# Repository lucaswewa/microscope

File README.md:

# microscope

Microscope control software. A Rust backend serves the microscope's camera, stage and the routines built on them (autofocus, calibration, slide scanning, timelapse) as [W3C Web of Things](https://www.w3.org/WoT/) Things over HTTP. A Vue 3 and TypeScript web app is the user interface.

- The backend is built on [`teta-wot`](https://github.com/lucaswewa/teta-wot), a Rust framework for Web of Things servers.
- The workflows and feature set are inspired by the [OpenFlexure Microscope](https://openflexure.org/), with an original interface and an independent implementation ([ADR-0002](docs/adr/0002-independent-implementation-of-openflexure-inspired-behaviour.md)). This project is not affiliated with the OpenFlexure project.

## Status

**Milestone 1 is complete:** the whole application, against a simulated camera and XYZ stage, whose images depend on the stage position and focus.

- **Its features match** the OpenFlexure Microscope's: live view, stage control, autofocus, calibration, slide scanning with stitching, timelapse sequences, a gallery, and the Settings, Logging, About and Power pages.
- **It ships a local launcher,** and the app connects to remote microscopes too.
- **The [plan's phase overview](docs/milestone-1/implementation-plan.md#8-phase-overview)** lists every phase, and the [retrospective](docs/milestone-1/retrospective.md) looks back on them.
- **Next:** real cameras and stages follow in milestone 2 ([readiness checklist](docs/milestone-2/readiness.md)), and the web app will later be reused in a Tauri desktop app.

Milestone 1 targets Windows x86_64 ([ADR-0003](docs/adr/0003-milestone-1-platform-windows-x86-64.md)).

## Using the microscope

### Getting it

Download `microscope-<version>-windows-x86_64.zip` from the [releases](https://github.com/lucaswewa/microscope/releases), and unzip it anywhere. It holds:

- `microscope-launcher.exe`, which you run;
- `microscope-server.exe`, which serves the microscope and the app;
- the default configuration, in `configs\`;
- this README, the licence, `NOTICE`, and the licences of the third-party software it includes.

### Running it

1. **Double-click `microscope-launcher.exe`.** A console window opens, and so does the app, in your browser, at <http://127.0.0.1:5000/>, or at another port if 5000 is taken. The window shows the server's messages; keep it open while you work.
2. **The first time,** the calibration wizard opens: follow it to calibrate the camera and how the stage moves in the image.
3. **To stop,** close the window or press Ctrl+C in it, or use the app's Power tab.
4. **Restart,** in the Power tab, starts the server again, and the app reconnects by itself. If the server ever crashes, the launcher starts it again.

Only one launcher runs at a time; a second one says so and ends.

### Where your data lives

Everything is in `%LOCALAPPDATA%\Microscope\` (paste that into File Explorer's address bar):

| Folder or file | What |
|---|---|
| `data\` | Your captures, scans and sequences, which the Gallery shows |
| `settings\` | Calibrations and settings |
| `logs\` | The server's daily logs, and `launcher.log`, everything the window showed |
| `generated-config.json` | The configuration the launcher gives the server; it's written at each start |

### Connecting from another computer

The launcher's server only answers this computer, unless you ask otherwise:

```powershell
.\microscope-launcher.exe --host 0.0.0.0
```

Then, on another computer on the same network, open `http://<this computer's name>:5000/` in a browser. From an app that's already open, use **Settings → Connection → Another microscope** with the same address, such as `lab-pc:5000`.

**There's no password:** anyone who can reach the computer can use the microscope. Do this only on a network you trust. Windows may ask whether to let the server through its firewall.

### Resetting

- **Settings and calibrations:** stop the launcher, delete `%LOCALAPPDATA%\Microscope\settings\`, and start it again. The calibration wizard opens, as the first time. Your captures and scans are kept.
- **Everything,** your captures and scans included: delete the whole `%LOCALAPPDATA%\Microscope\` folder.

### Other options

`microscope-launcher.exe --help` lists them:

- `-c <file>` uses another configuration;
- `--root <folder>` keeps the data somewhere other than `%LOCALAPPDATA%\Microscope\`;
- `--port <number>` prefers another port;
- `--no-browser` doesn't open the app.

### A Zaber stage

[`configs/zaber.json`](configs/zaber.json) drives a Zaber XYZ stage, with the simulated camera ([ADR-0042](docs/adr/0042-zaber-stages-through-the-ascii-protocol.md)):

1. **Find its port:** `microscope-server --list-devices` lists the serial ports.
2. **Configure it:** in a copy of the file, set `port`, such as `COM3` or `/dev/ttyUSB0`. Check each axis's `device` and `axis` numbers; the defaults suit three integrated stages, daisy-chained. Set each axis's `microstep_um`, from its datasheet, for distances in µm.
3. **Run it:** `microscope-launcher -c my-zaber.json`.
4. **Home it,** once the stage is clear, from Settings → Stage. z homes too.

The simulated camera's image doesn't follow the Zaber stage, so autofocus and scans won't work with this file. A real camera's configuration follows with its driver.

### A Basler camera

[`configs/basler-zaber.json`](configs/basler-zaber.json) drives a Basler camera, through [pylon](https://www.baslerweb.com/pylon), and a Zaber stage ([ADR-0044](docs/adr/0044-one-camera-thing-for-every-sdk.md)):

1. **Install pylon,** and plug the camera in. `microscope-server --list-devices` lists it, by serial number.
2. **Configure it:** in a copy of the file, set the camera's `serial_number`, or leave it out for the first camera found, and the stage as above.
3. **Run it,** and calibrate the camera from Settings → Camera, looking at the empty slide: the camera's own automatic exposure and white balance run once, then the background is set.

Settings → Camera has the camera's exposure, gain, pixel format, white balance and binning, as far as it has them. If the camera is unplugged, the server opens it again once it's back.

Without a camera, pylon's emulator stands in: set `PYLON_CAMEMU=1` before starting the server, and the camera `0815-0000` appears.

### On Linux

Linux x86_64 and ARM64, the Raspberry Pi 5 included, have two downloads.

**`microscope-<version>-linux-<arch>.tar.gz`** runs the microscope as on Windows. Unpack it, and run `./microscope-launcher` in a terminal. Everything is in `~/.local/share/microscope/` (or in `$XDG_DATA_HOME`, if that's set), in the same folders as above. Ctrl+C, or closing the terminal, stops it.

**`microscope_<version>_<arch>.deb`** runs the microscope as a service, started at boot, such as on a Pi with no screen:

```sh
sudo apt install ./microscope_0.2.0_arm64.deb
```

- **It serves** <http://127.0.0.1:5000/>, to this machine alone, as the server has no password yet. To reach it from other computers, on a network you trust, set `MICROSCOPE_HOST=0.0.0.0` in `/etc/default/microscope`, then run `sudo systemctl restart microscope`.
- **Its microscope** is in `/etc/microscope/config.json`: the simulated one, at first. Its settings and data are in `/var/lib/microscope/`, and its logs in `/var/log/microscope/` and in `journalctl -u microscope`.
- **Restart,** in the Power tab, starts it again. **Shut down** stops it until `sudo systemctl start microscope`, or the next boot. If it crashes, systemd starts it again; the sixth crash in a minute stops it.
- **Removing it,** `sudo apt remove microscope`, stops the service and keeps `/var/lib/microscope/`.

## Documentation

- [Milestone 1 goals](docs/milestone-1/goals.md)
- [Milestone 1 implementation plan](docs/milestone-1/implementation-plan.md) and [phase specifications](docs/milestone-1/phases.md)
- [Architecture decision records](docs/adr/README.md)
- [Implementation notes](docs/milestone-1/notes/README.md), one per phase, and the [milestone's retrospective](docs/milestone-1/retrospective.md)
- [Milestone 2 readiness checklist](docs/milestone-2/readiness.md)

## Development

### Prerequisites

- Windows x86_64.
- [rustup](https://rustup.rs/), with the MSVC toolchain and Visual Studio's C++ build tools. The repository pins its compiler (Rust 1.98.1) in `rust-toolchain.toml`; `rustup toolchain install` in the repository installs it.
- [Node.js](https://nodejs.org/) 24 LTS, with npm, for the web app.

### Build and check

These are the checks CI runs:

```powershell
cargo fmt --all --check
cargo clippy --workspace --all-targets --locked -- -D warnings
cargo test --workspace --locked
cargo doc --workspace --no-deps --locked   # CI sets RUSTDOCFLAGS=-D warnings
```

### Run the server

```powershell
cargo run -p microscope-server -- -c configs/simulation.json
```

It listens on <http://127.0.0.1:5000/> (`--host` and `--port` change that). The API is under `/api/v1` (for example <http://127.0.0.1:5000/api/v1/health> and <http://127.0.0.1:5000/api/v1/system/>), and the interactive API docs are at <http://127.0.0.1:5000/docs>. Ctrl-C stops it gracefully. `--help` lists the options: `teta-wot`'s, and `--webapp-dir`.

The server also serves the web app, at <http://127.0.0.1:5000/> ([ADR-0016](docs/adr/0016-serving-and-embedding-the-web-app.md)). A debug build reads it from `web/dist`, so build the web app first (`npm run build` in `web/`); without a build, `/` shows a placeholder page. `--webapp-dir <path>` serves it from another folder.

`--list-devices` prints the serial ports and the cameras the drivers find, for writing a configuration ([configs/README.md](configs/README.md)). Basler cameras need [pylon](https://www.baslerweb.com/pylon), and Allied Vision's [Vimba X](https://www.alliedvision.com/en/products/software/vimba-x-sdk/), installed; the server runs without them ([ADR-0041](docs/adr/0041-hardware-drivers.md)).

### Build a release

Build the web app first, then the server, which embeds `web/dist`:

```powershell
cd web
npm ci
npm run build
cd ..
cargo build --release -p microscope-server
```

`target/release/microscope-server.exe -c configs/simulation.json` then serves the API and the app on its own.

The zip a user downloads also needs the launcher's release build and [cargo-about](https://github.com/EmbarkStudios/cargo-about), which lists the Rust crates' licences ([ADR-0035](docs/adr/0035-release-packaging-and-third-party-notices.md)):

```powershell
cargo build --release -p microscope-server -p microscope-launcher --locked
cargo install cargo-about --version 0.9.2 --features cli --locked
./release/package.ps1 -Version 0.2.0
```

It's written to `release-out\`. On Linux, `bash release/package.sh 0.2.0` builds the archive and the `.deb` there instead, with `jq` and `dpkg-deb`. Pushing a tag such as `v0.2.0` has the release workflow build them all, check that each launcher starts and that the `.deb`'s service serves and restarts, and publish them, with the tag's notes from `release/notes/` where there are some.

### Run the launcher

The launcher is the one command a user needs ([ADR-0033](docs/adr/0033-local-launcher-and-its-tauri-successor.md)). It keeps the server's settings, data and logs in `%LOCALAPPDATA%\Microscope`, or on Linux in `~/.local/share/microscope`, starts the server on port 5000 (or another, if that's taken), and opens the app in the browser. It starts the server again when the server asks to restart, or after a crash. Ctrl-C stops both.

```powershell
cargo build -p microscope-server -p microscope-launcher
target\debug\microscope-launcher.exe
```

It runs the `microscope-server` beside it, so build both; a release build, after the web app, gives a server with the app embedded. `-c <config>` uses another configuration, `--no-browser` doesn't open the app, `--root <folder>` keeps everything in another folder, and `--help` lists the rest. Everything the server prints also goes to `logs\launcher.log` in that folder.

Logs go to the console, to daily files in `.microscope/logs/`, and to the server log at <http://127.0.0.1:5000/api/v1/log/>; `/api/v1/logfile/` downloads today's file. `--debug` adds DEBUG events from the application and `teta-wot` ([ADR-0008](docs/adr/0008-server-logging-and-log-endpoints.md)).

The workspace's crates and the rules between them are described in [ADR-0005](docs/adr/0005-repository-layout-and-crate-boundaries.md).

### The web app

The web app is in `web/` ([ADR-0009](docs/adr/0009-frontend-toolchain.md)):

```powershell
cd web
npm ci
npm run dev          # http://localhost:5173/, with /api forwarded to the server on port 5000
```

These are the checks CI runs, plus the end-to-end tests:

```powershell
npm run format:check
npm run lint
npm run typecheck
npm run test:unit
npm run build
npx playwright install chromium   # once per machine
npm run test:e2e                  # builds the app and a server that serves it, on ports 5098 and 5099
```

The end-to-end tests' server keeps its settings, data and logs in a temporary folder, emptied for each run, not in `.microscope`. They include whole workflows, such as a histo scan, and Restart through the launcher, which they build.

The long tests run each night in CI ([`nightly.yml`](.github/workflows/nightly.yml)): a 30-minute soak, streaming and scanning, and the performance budgets. To run them, preferably against a release build:

```powershell
$env:MICROSCOPE_LONG = '1'; $env:MICROSCOPE_SOAK_MINUTES = '30'
npx playwright test --project=long   # soak.json and budgets.json are written under test-results
```

`npm run test:contract` runs the web app's WoT client against a running server, whose API root is `MICROSCOPE_API_URL` (by default `http://127.0.0.1:5000/api/v1/`). CI runs it against a fresh server.

`MICROSCOPE_API_TARGET` points the development proxy at another server, such as `http://lab-pc:5000`.

Two pages exist only in development, each showing light and dark side by side:

- <http://localhost:5173/#/dev/tokens> shows the design tokens ([ADR-0011](docs/adr/0011-design-tokens-and-theming.md));
- <http://localhost:5173/#/dev/components> shows every UI component, with their states and overlays ([ADR-0013](docs/adr/0013-own-components-on-reka-ui-primitives.md)).

Both have an **Accent** picker, to try every accent colour across the whole app: the nine that Settings, Display offers, and 19 more ([ADR-0047](docs/adr/0047-accent-colours-a-person-can-choose.md)). It's the same choice as Settings', kept in this browser. The tokens page shows each pair's contrast in both themes, with those below WCAG AA's minimum in red.

The rules that keep the app ready for a Tauri desktop app are in [ADR-0010](docs/adr/0010-rules-for-a-tauri-ready-web-app.md).

### Contributing

Work proceeds in small phases, each delivered as one pull request that follows the [Definition of Done](docs/milestone-1/implementation-plan.md#7-how-phases-work). [CLAUDE.md](CLAUDE.md) sums up the working rules, for people and for Claude Code sessions.

## Licence

[MIT](LICENSE). Third-party material and its licences are listed in [NOTICE](NOTICE).

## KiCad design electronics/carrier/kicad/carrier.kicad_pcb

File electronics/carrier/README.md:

# The OPTIMA carrier board

The board under the Pico 2. [`optima_carrier_board.md`](../../docs/misc/optima_carrier_board.md) describes it, [`kicad/carrier.pdf`](kicad/carrier.pdf) is its schematic, and [`kicad/fab/`](kicad/fab/) has what a maker needs.

## Changing it

Don't edit the schematic or the board in KiCad: the build replaces them.

1. Change [`circuit.py`](circuit.py) or [`placement.py`](placement.py).
2. Run the build, with KiCad 10 installed:

   ```sh
   python electronics/carrier/make.py
   ```

   It takes about 15 seconds, and prints every check.
3. If you moved a part, or changed a net, route it again (below). The checks fail until you do.
4. Commit the scripts with the rebuilt `kicad/`, `routes.ses` and `REPORT.md`.

`python electronics/carrier/make.py --check` builds into a temporary folder instead. It fails if a check fails, or if `kicad/` or `REPORT.md` isn't what the scripts build. Run it before every pull request. It doesn't compare the PDFs, the Gerbers' zip or the picture, which the rest stand for, or the fill of the pour, which KiCad changes by a few points from run to run.

## Routing it

The build doesn't need a router: it takes the tracks from `routes.ses`. Only a new route needs FreeRouting, which is a tool here, not part of this project:

1. Download `freerouting-2.5.0.jar` from [its release](https://github.com/freerouting/freerouting/releases/tag/v2.5.0), and a Java 25 runtime, such as [Temurin's](https://adoptium.net/temurin/releases/?version=25). Neither needs installing.
2. Run this, leaving out `JAVA` if `java` on your path is Java 25:

   ```sh
   FREEROUTING=path/to/freerouting-2.5.0.jar JAVA=path/to/java python electronics/carrier/make.py --route
   ```

It takes about a minute, and prints how many connections are open after each job. A new route gives a different board each time, so run it again if it stops short of 0, or if a check fails. Then read the copper: the DRC doesn't know about current.

What took some finding, in case FreeRouting changes:

- **The jar, not the command-line build.** Version 2.5.0's `freerouting-cli` crashes on its first board and then hangs ([#957](https://github.com/freerouting/freerouting/issues/957), [#1019](https://github.com/freerouting/freerouting/issues/1019)).
- **A chain of one-pass jobs.** A job's first pass does the work, and its later passes tear up about the GND net's worth of it. So each job starts from the last one's tracks.
- **GND as a net, not a plane.** As a plane, the router counts it as joined while its own tracks cut the pour into islands.
- **Cheaper vias.** At its own cost, it leaves crossings open sooner than use one.
- **Separate processes.** KiCad reads the project's net classes only when it loads a saved board in a new process, or it exports every net in one class. So `board.py` runs in steps.
- **Its options,** in `make.py`. Automatic narrowing and fan-out make tracks thinner than their class. Usage data goes out unless it's turned off, which `make.py` does.

FreeRouting leaves its settings and logs in your user folder: `AppData\Roaming\freerouting` and `AppData\Local\freerouting` on Windows.

## Files

| File | What it does |
|---|---|
| `circuit.py` | The parts and the nets that join their pins |
| `schematic.py` | Draws the circuit as a KiCad schematic, with this board's symbols, and writes the project, with its rules and net classes |
| `footprints.py` | The two footprints KiCad doesn't have |
| `placement.py` | Where each part goes, and the tracks laid out by hand |
| `board.py` | Builds the board in KiCad's Python: the parts, the fixed tracks, the routes and the pour |
| `routes.ses` | The router's tracks. FreeRouting writes this. |
| `checks.py` | Checks the netlist against the circuit, the interlock, the pins, levels and connectors, and the board |
| `make.py` | Runs all that, and KiCad's command line for its checks and the fabrication files |
| `kicad/` | The built KiCad project, netlist and PDF, with the fabrication files in `kicad/fab/` |
| `REPORT.md` | The checks' results |

The symbols and those two footprints are this project's own. The other footprints are named from KiCad's libraries, which allow it.

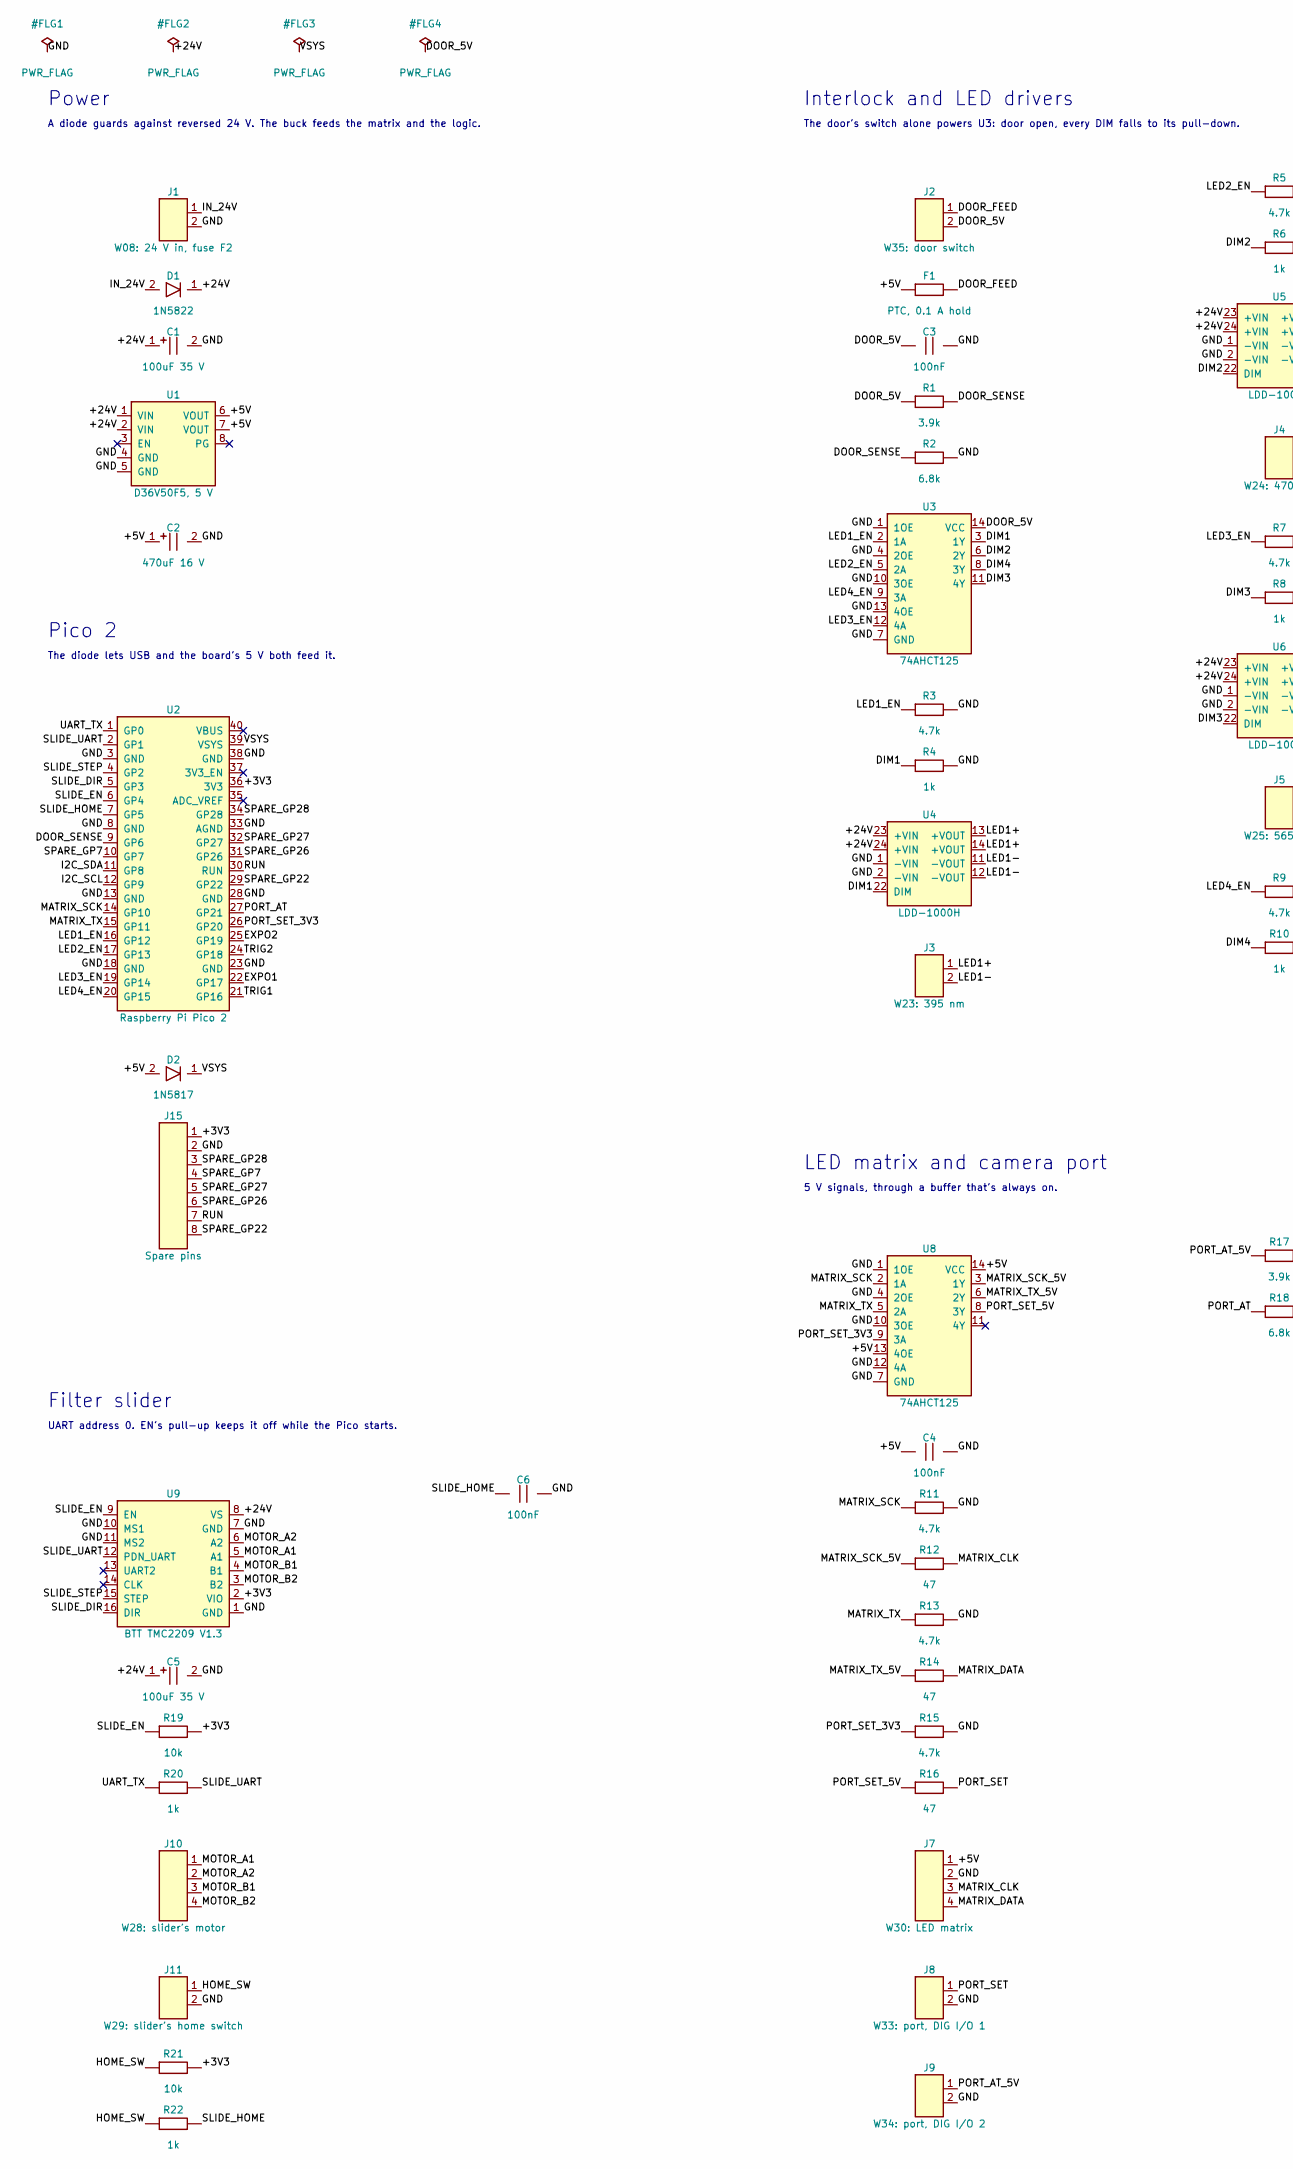
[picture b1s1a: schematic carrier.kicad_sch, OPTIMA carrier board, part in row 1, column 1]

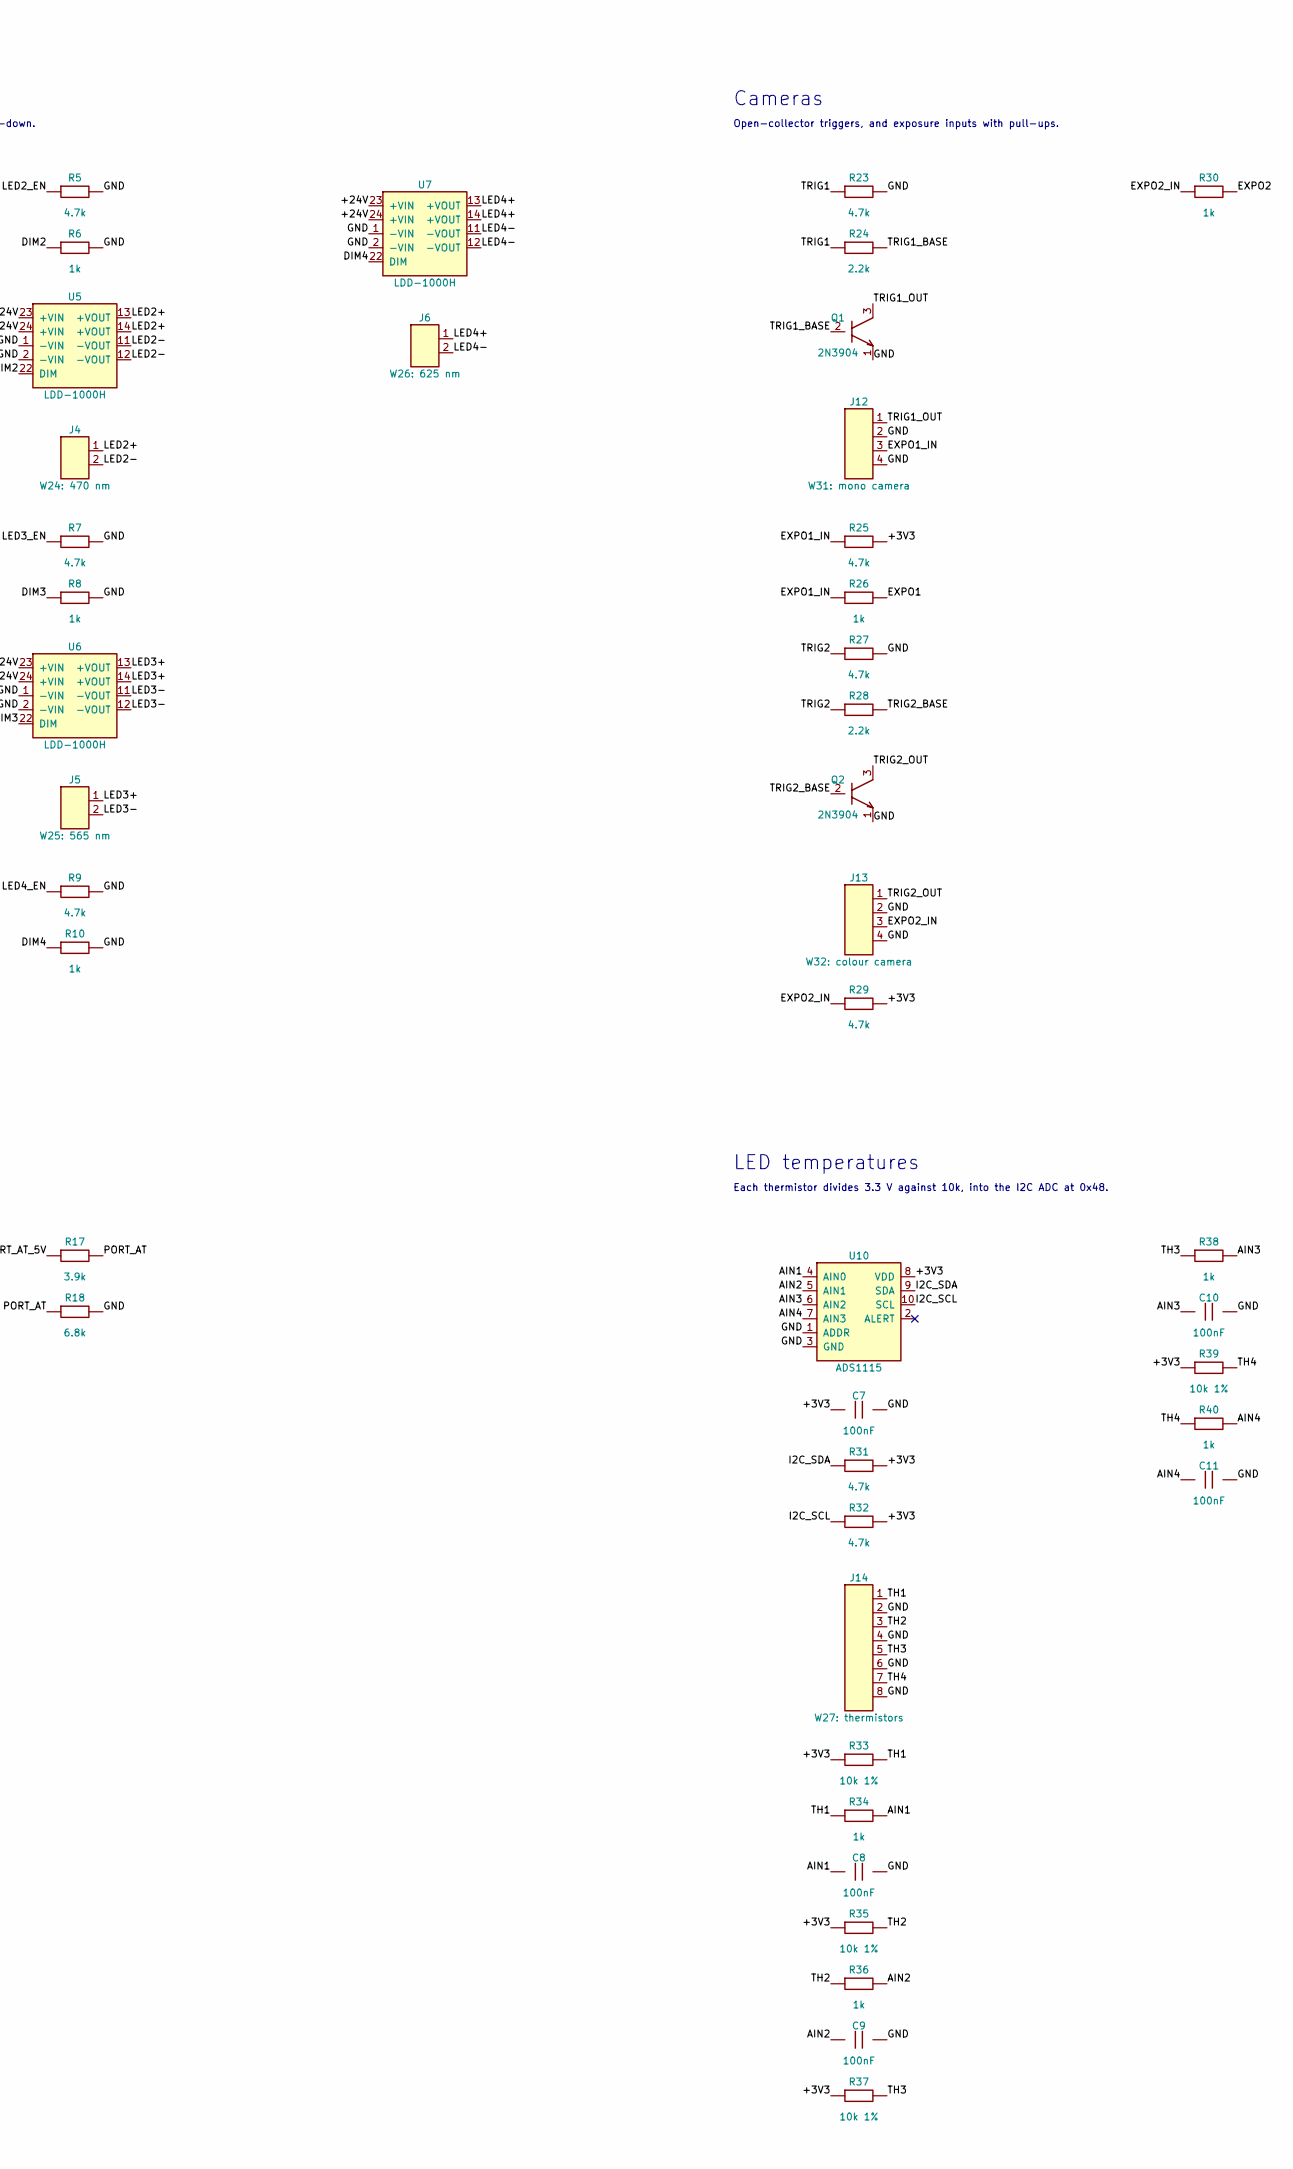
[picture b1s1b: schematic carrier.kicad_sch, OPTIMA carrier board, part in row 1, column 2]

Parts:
C1, C5: 100uF 35 V; CP_Radial_D10.0mm_P5.00mm
C2: 470uF 16 V; CP_Radial_D10.0mm_P5.00mm
C3, C4, C6, C7, C8, C9, C10, C11: 100nF; C_Disc_D4.7mm_W2.5mm_P5.00mm
D1: 1N5822; D_DO-201AD_P15.24mm_Horizontal
D2: 1N5817; D_DO-41_SOD81_P10.16mm_Horizontal
F1: PTC, 0.1 A hold; C_Disc_D7.5mm_W2.5mm_P5.00mm
J1: W08: 24 V in, fuse F2; TerminalBlock_Phoenix_MKDS-1,5-2-5.08_1x02_P5.08mm_Horizont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
J2: W35: door switch; JST_XH_B2B-XH-A_1x02_P2.50mm_Vertical
J3: W23: 395 nm; TerminalBlock_Phoenix_MKDS-1,5-2-5.08_1x02_P5.08mm_Horizont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
J4: W24: 470 nm; TerminalBlock_Phoenix_MKDS-1,5-2-5.08_1x02_P5.08mm_Horizont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
J5: W25: 565 nm; TerminalBlock_Phoenix_MKDS-1,5-2-5.08_1x02_P5.08mm_Horizont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
J6: W26: 625 nm; TerminalBlock_Phoenix_MKDS-1,5-2-5.08_1x02_P5.08mm_Horizont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
J7: W30: LED matrix; TerminalBlock_Phoenix_MKDS-1,5-4-5.08_1x04_P5.08mm_Horizont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
J8: W33: port, DIG I/O 1; JST_XH_B2B-XH-A_1x02_P2.50mm_Vertical
J9: W34: port, DIG I/O 2; JST_XH_B2B-XH-A_1x02_P2.50mm_Vertical
J10: W28: slider's motor; JST_XH_B4B-XH-A_1x04_P2.50mm_Vertical
J11: W29: slider's home switch; JST_XH_B2B-XH-A_1x02_P2.50mm_Vertical
J12: W31: mono camera; JST_XH_B4B-XH-A_1x04_P2.50mm_Vertical
J13: W32: colour camera; JST_XH_B4B-XH-A_1x04_P2.50mm_Vertical
J14: W27: thermistors; JST_XH_B8B-XH-A_1x08_P2.50mm_Vertical
J15: Spare pins; PinHeader_1x08_P2.54mm_Vertical
Q1, Q2: 2N3904; TO-92_Inline_Wide
R1, R17: 3.9k; R_Axial_DIN0207_L6.3mm_D2.5mm_P2.54mm_Vertical
R2, R18: 6.8k; R_Axial_DIN0207_L6.3mm_D2.5mm_P2.54mm_Vertical
R3, R5, R7, R9, R11, R13, R15, R23, R25, R27, R29, R31, R32: 4.7k; R_Axial_DIN0207_L6.3mm_D2.5mm_P2.54mm_Vertical
R4, R6, R8, R10, R20, R22, R26, R30, R34, R36, R38, R40: 1k; R_Axial_DIN0207_L6.3mm_D2.5mm_P2.54mm_Vertical
R12, R14, R16: 47; R_Axial_DIN0207_L6.3mm_D2.5mm_P2.54mm_Vertical
R19, R21: 10k; R_Axial_DIN0207_L6.3mm_D2.5mm_P2.54mm_Vertical
R24, R28: 2.2k; R_Axial_DIN0207_L6.3mm_D2.5mm_P2.54mm_Vertical
R33, R35, R37, R39: 10k 1%; R_Axial_DIN0207_L6.3mm_D2.5mm_P2.54mm_Vertical
U1: D36V50F5, 5 V; D36V50F5
U2: Raspberry Pi Pico 2; RaspberryPi_Pico_Common_THT
U3, U8: 74AHCT125; DIP-14_W7.62mm
U4, U5, U6, U7: LDD-1000H; LDD-H
U9: BTT TMC2209 V1.3; Pololu_Breakout-16_15.2x20.3mm
U10: ADS1115; TSSOP-10_3x3mm_P0.5mm

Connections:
/+3V3: C7.1, J15.1, R19.2, R21.2, R25.2, R29.2, R31.2, R32.2, R33.1, R35.1, R37.1, R39.1, U2.36 (3V3), U9.2 (VIO), U10.8 (VDD)
/+5V: C2.1, C4.1, D2.2, F1.1, J7.1, U1.6 (VOUT), U1.7 (VOUT), U8.13 (4OE), U8.14 (VCC)
/+24V: C1.1, C5.1, D1.1, U1.1 (VIN), U1.2 (VIN), U4.23 (+VIN), U4.24 (+VIN), U5.23 (+VIN), U5.24 (+VIN), U6.23 (+VIN), U6.24 (+VIN), U7.23 (+VIN), U7.24 (+VIN), U9.8 (VS)
/AIN1: C8.1, R34.2, U10.4 (AIN0)
/AIN2: C9.1, R36.2, U10.5 (AIN1)
/AIN3: C10.1, R38.2, U10.6 (AIN2)
/AIN4: C11.1, R40.2, U10.7 (AIN3)
/DIM1: R4.1, U3.3 (1Y), U4.22 (DIM)
/DIM2: R6.1, U3.6 (2Y), U5.22 (DIM)
/DIM3: R8.1, U3.11 (4Y), U6.22 (DIM)
/DIM4: R10.1, U3.8 (3Y), U7.22 (DIM)
/DOOR_5V: C3.1, J2.2, R1.1, U3.14 (VCC)
/DOOR_FEED: F1.2, J2.1
/DOOR_SENSE: R1.2, R2.1, U2.9 (GP6)
/EXPO1: R26.2, U2.22 (GP17)
/EXPO1_IN: J12.3, R25.1, R26.1
/EXPO2: R30.2, U2.25 (GP19)
/EXPO2_IN: J13.3, R29.1, R30.1
/GND: C1.2, C2.2, C3.2, C4.2, C5.2, C6.2, C7.2, C8.2, C9.2, C10.2, C11.2, J1.2, J7.2, J8.2, J9.2, J11.2, J12.2, J12.4, J13.2, J13.4, J14.2, J14.4, J14.6, J14.8, J15.2, Q1.1 (E), Q2.1 (E), R2.2, R3.2, R4.2, R5.2, R6.2, R7.2, R8.2, R9.2, R10.2, R11.2, R13.2, R15.2, R18.2, R23.2, R27.2, U1.4 (GND), U1.5 (GND), U2.3 (GND), U2.8 (GND), U2.13 (GND), U2.18 (GND), U2.23 (GND), U2.28 (GND), U2.33 (AGND), U2.38 (GND), U3.1 (1OE), U3.4 (2OE), U3.7 (GND), U3.10 (3OE), U3.13 (4OE), U4.1 (-VIN), U4.2 (-VIN), U5.1 (-VIN), U5.2 (-VIN), U6.1 (-VIN), U6.2 (-VIN), U7.1 (-VIN), U7.2 (-VIN), U8.1 (1OE), U8.4 (2OE), U8.7 (GND), U8.10 (3OE), U8.12 (4A), U9.1 (GND), U9.7 (GND), U9.10 (MS1), U9.11 (MS2), U10.1 (ADDR), U10.3 (GND)
/HOME_SW: J11.1, R21.1, R22.1
/I2C_SCL: R32.1, U2.12 (GP9), U10.10 (SCL)
/I2C_SDA: R31.1, U2.11 (GP8), U10.9 (SDA)
/IN_24V: D1.2, J1.1
/LED1+: J3.1, U4.13 (+VOUT), U4.14 (+VOUT)
/LED1-: J3.2, U4.11 (-VOUT), U4.12 (-VOUT)
/LED1_EN: R3.1, U2.16 (GP12), U3.2 (1A)
/LED2+: J4.1, U5.13 (+VOUT), U5.14 (+VOUT)
/LED2-: J4.2, U5.11 (-VOUT), U5.12 (-VOUT)
/LED2_EN: R5.1, U2.17 (GP13), U3.5 (2A)
/LED3+: J5.1, U6.13 (+VOUT), U6.14 (+VOUT)
/LED3-: J5.2, U6.11 (-VOUT), U6.12 (-VOUT)
/LED3_EN: R7.1, U2.19 (GP14), U3.12 (4A)
/LED4+: J6.1, U7.13 (+VOUT), U7.14 (+VOUT)
/LED4-: J6.2, U7.11 (-VOUT), U7.12 (-VOUT)
/LED4_EN: R9.1, U2.20 (GP15), U3.9 (3A)
/MATRIX_CLK: J7.3, R12.2
/MATRIX_DATA: J7.4, R14.2
/MATRIX_SCK: R11.1, U2.14 (GP10), U8.2 (1A)
/MATRIX_SCK_5V: R12.1, U8.3 (1Y)
/MATRIX_TX: R13.1, U2.15 (GP11), U8.5 (2A)
/MATRIX_TX_5V: R14.1, U8.6 (2Y)
/MOTOR_A1: J10.1, U9.5 (A1)
/MOTOR_A2: J10.2, U9.6 (A2)
/MOTOR_B1: J10.3, U9.4 (B1)
/MOTOR_B2: J10.4, U9.3 (B2)
/PORT_AT: R17.2, R18.1, U2.27 (GP21)
/PORT_AT_5V: J9.1, R17.1
/PORT_SET: J8.1, R16.2
/PORT_SET_3V3: R15.1, U2.26 (GP20), U8.9 (3A)
/PORT_SET_5V: R16.1, U8.8 (3Y)
/RUN: J15.7, U2.30 (RUN)
/SLIDE_DIR: U2.5 (GP3), U9.16 (DIR)
/SLIDE_EN: R19.1, U2.6 (GP4), U9.9 (EN)
/SLIDE_HOME: C6.1, R22.2, U2.7 (GP5)
/SLIDE_STEP: U2.4 (GP2), U9.15 (STEP)
/SLIDE_UART: R20.2, U2.2 (GP1), U9.12 (PDN_UART)
/SPARE_GP7: J15.4, U2.10 (GP7)
/SPARE_GP22: J15.8, U2.29 (GP22)
/SPARE_GP26: J15.6, U2.31 (GP26)
/SPARE_GP27: J15.5, U2.32 (GP27)
/SPARE_GP28: J15.3, U2.34 (GP28)
/TH1: J14.1, R33.2, R34.1
/TH2: J14.3, R35.2, R36.1
/TH3: J14.5, R37.2, R38.1
/TH4: J14.7, R39.2, R40.1
/TRIG1: R23.1, R24.1, U2.21 (GP16)
/TRIG1_BASE: Q1.2 (B), R24.2
/TRIG1_OUT: J12.1, Q1.3 (C)
/TRIG2: R27.1, R28.1, U2.24 (GP18)
/TRIG2_BASE: Q2.2 (B), R28.2
/TRIG2_OUT: J13.1, Q2.3 (C)
/UART_TX: R20.1, U2.1 (GP0)
/VSYS: D2.1, U2.39 (VSYS)

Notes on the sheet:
Power
A diode guards against reversed 24 V. The buck feeds the matrix and the logic.
Pico 2
The diode lets USB and the board's 5 V both feed it.
Filter slider
UART address 0. EN's pull-up keeps it off while the Pico starts.
Interlock and LED drivers
The door's switch alone powers U3: door open, every DIM falls to its pull-down.
LED matrix and camera port
5 V signals, through a buffer that's always on.
Cameras
Open-collector triggers, and exposure inputs with pull-ups.
LED temperatures
Each thermistor divides 3.3 V against 10k, into the I2C ADC at 0x48.

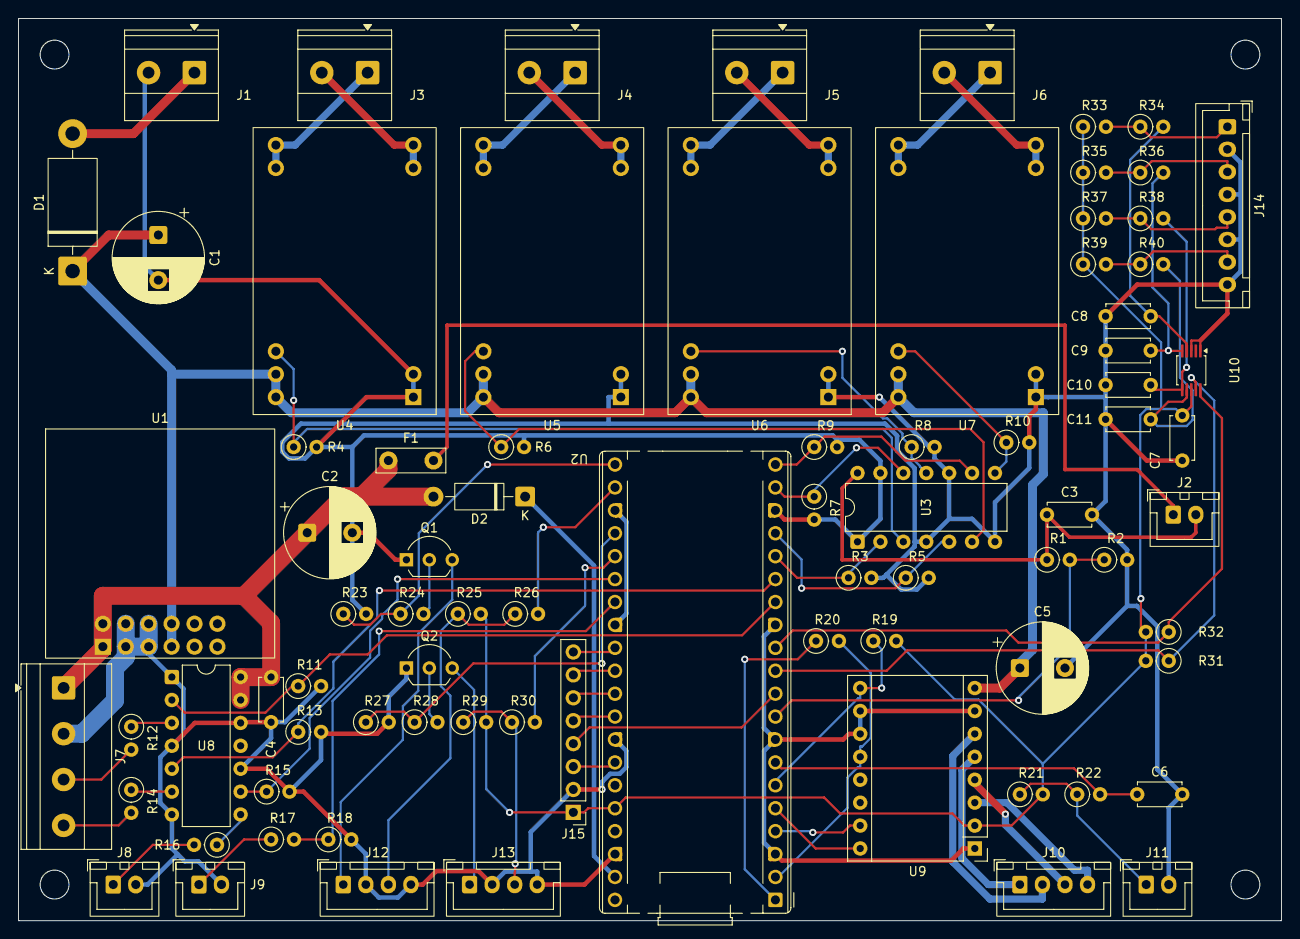
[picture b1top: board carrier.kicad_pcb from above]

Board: 2 copper layers, 140.0 x 100.0 mm, 85 parts (0 on the bottom side), 73 nets.

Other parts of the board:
H1, H2, H3, H4: MountingHole_3.2mm_M3

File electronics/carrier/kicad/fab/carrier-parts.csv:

Quantity,Part,Footprint,References
8,"100nF","C_Disc_D4.7mm_W2.5mm_P5.00mm","C3 C4 C6 C7 C8 C9 C10 C11"
2,"100uF 35 V","CP_Radial_D10.0mm_P5.00mm","C1 C5"
2,"10k","R_Axial_DIN0207_L6.3mm_D2.5mm_P2.54mm_Vertical","R19 R21"
4,"10k 1%","R_Axial_DIN0207_L6.3mm_D2.5mm_P2.54mm_Vertical","R33 R35 R37 R39"
1,"1N5817","D_DO-41_SOD81_P10.16mm_Horizontal","D2"
1,"1N5822","D_DO-201AD_P15.24mm_Horizontal","D1"
12,"1k","R_Axial_DIN0207_L6.3mm_D2.5mm_P2.54mm_Vertical","R4 R6 R8 R10 R20 R22 R26 R30 R34 R36 R38 R40"
2,"2.2k","R_Axial_DIN0207_L6.3mm_D2.5mm_P2.54mm_Vertical","R24 R28"
2,"2N3904","TO-92_Inline_Wide","Q1 Q2"
2,"3.9k","R_Axial_DIN0207_L6.3mm_D2.5mm_P2.54mm_Vertical","R1 R17"
13,"4.7k","R_Axial_DIN0207_L6.3mm_D2.5mm_P2.54mm_Vertical","R3 R5 R7 R9 R11 R13 R15 R23 R25 R27 R29 R31 R32"
3,"47","R_Axial_DIN0207_L6.3mm_D2.5mm_P2.54mm_Vertical","R12 R14 R16"
1,"470uF 16 V","CP_Radial_D10.0mm_P5.00mm","C2"
2,"6.8k","R_Axial_DIN0207_L6.3mm_D2.5mm_P2.54mm_Vertical","R2 R18"
2,"74AHCT125","DIP-14_W7.62mm","U3 U8"
1,"ADS1115","TSSOP-10_3x3mm_P0.5mm","U10"
1,"BTT TMC2209 V1.3","Pololu_Breakout-16_15.2x20.3mm","U9"
1,"D36V50F5, 5 V","D36V50F5","U1"
4,"LDD-1000H","LDD-H","U4 U5 U6 U7"
1,"PTC, 0.1 A hold","C_Disc_D7.5mm_W2.5mm_P5.00mm","F1"
1,"Raspberry Pi Pico 2","RaspberryPi_Pico_Common_THT","U2"
1,"Spare pins","PinHeader_1x08_P2.54mm_Vertical","J15"
1,"W08: 24 V in, fuse F2","TerminalBlock_Phoenix_MKDS-1,5-2-5.08_1x02_P5.08mm_Horizontal","J1"
1,"W23: 395 nm","TerminalBlock_Phoenix_MKDS-1,5-2-5.08_1x02_P5.08mm_Horizontal","J3"
1,"W24: 470 nm","TerminalBlock_Phoenix_MKDS-1,5-2-5.08_1x02_P5.08mm_Horizontal","J4"
1,"W25: 565 nm","TerminalBlock_Phoenix_MKDS-1,5-2-5.08_1x02_P5.08mm_Horizontal","J5"
1,"W26: 625 nm","TerminalBlock_Phoenix_MKDS-1,5-2-5.08_1x02_P5.08mm_Horizontal","J6"
1,"W27: thermistors","JST_XH_B8B-XH-A_1x08_P2.50mm_Vertical","J14"
1,"W28: slider's motor","JST_XH_B4B-XH-A_1x04_P2.50mm_Vertical","J10"
1,"W29: slider's home switch","JST_XH_B2B-XH-A_1x02_P2.50mm_Vertical","J11"
1,"W30: LED matrix","TerminalBlock_Phoenix_MKDS-1,5-4-5.08_1x04_P5.08mm_Horizontal","J7"
1,"W31: mono camera","JST_XH_B4B-XH-A_1x04_P2.50mm_Vertical","J12"
1,"W32: colour camera","JST_XH_B4B-XH-A_1x04_P2.50mm_Vertical","J13"
1,"W33: port, DIG I/O 1","JST_XH_B2B-XH-A_1x02_P2.50mm_Vertical","J8"
1,"W34: port, DIG I/O 2","JST_XH_B2B-XH-A_1x02_P2.50mm_Vertical","J9"
1,"W35: door switch","JST_XH_B2B-XH-A_1x02_P2.50mm_Vertical","J2"

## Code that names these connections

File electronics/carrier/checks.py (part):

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            continue
        buffer = next(refs[r] for r, _ in all_nets[dim] if refs[r].kind == "74AHCT125")
        gate_in = buffer.pins[GATES[next(n for n, net in buffer.pins.items() if net == dim)]]
        if buffer.pins[14] != "DOOR_5V":
            wrong.append("%s's buffer runs from %s" % (dim, buffer.pins[14]))
        if not resistor(dim, "GND") or DIM_SOURCE * resistor(dim, "GND") >= LDD_OFF:
            wrong.append("%s has no pull-down that holds it off" % dim)
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    bad_pins = [n for n, pins in FUNCTIONS.items() if not any(g in pins and gpio[g] == n for g in gpio)]
    # 5 V signals: the supplies, the camera port's output and the buffers' outputs.
    buffers = [p for p in PARTS if p.kind == "74AHCT125"]
    high = {"+5V", "DOOR_5V", "DOOR_FEED", "PORT_AT_5V"} | {p.pins[y] for p in buffers for y in GATES}
    high &= set(gpio.values())
    levels = {}
    for top, net in (("DOOR_5V", "DOOR_SENSE"), ("PORT_AT_5V", "PORT_AT")):
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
